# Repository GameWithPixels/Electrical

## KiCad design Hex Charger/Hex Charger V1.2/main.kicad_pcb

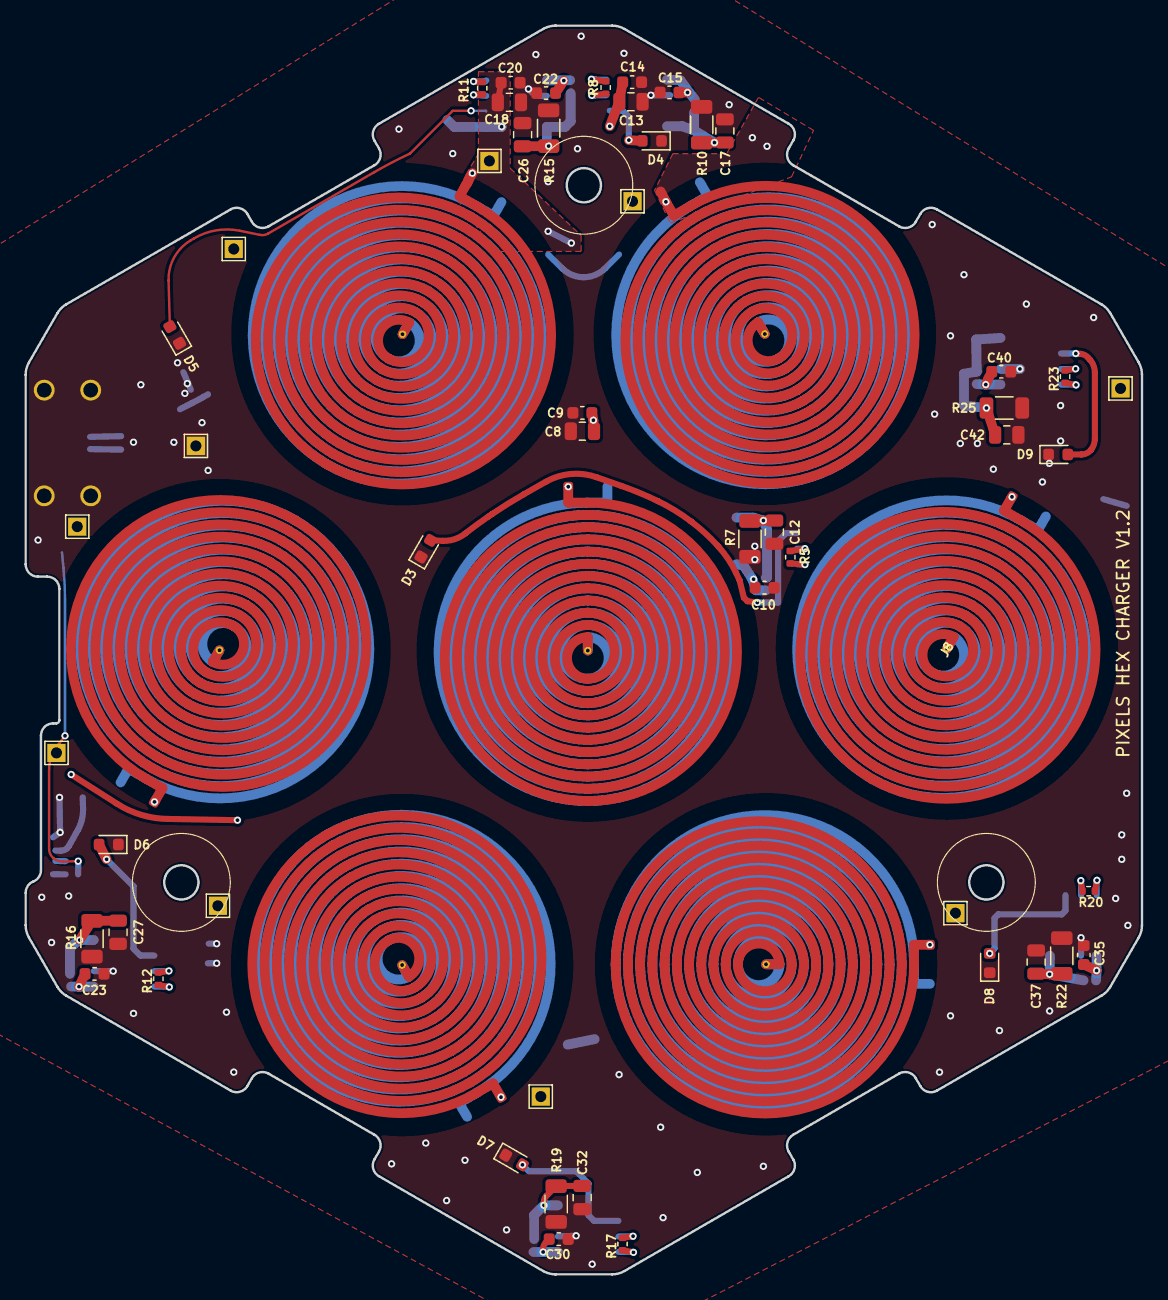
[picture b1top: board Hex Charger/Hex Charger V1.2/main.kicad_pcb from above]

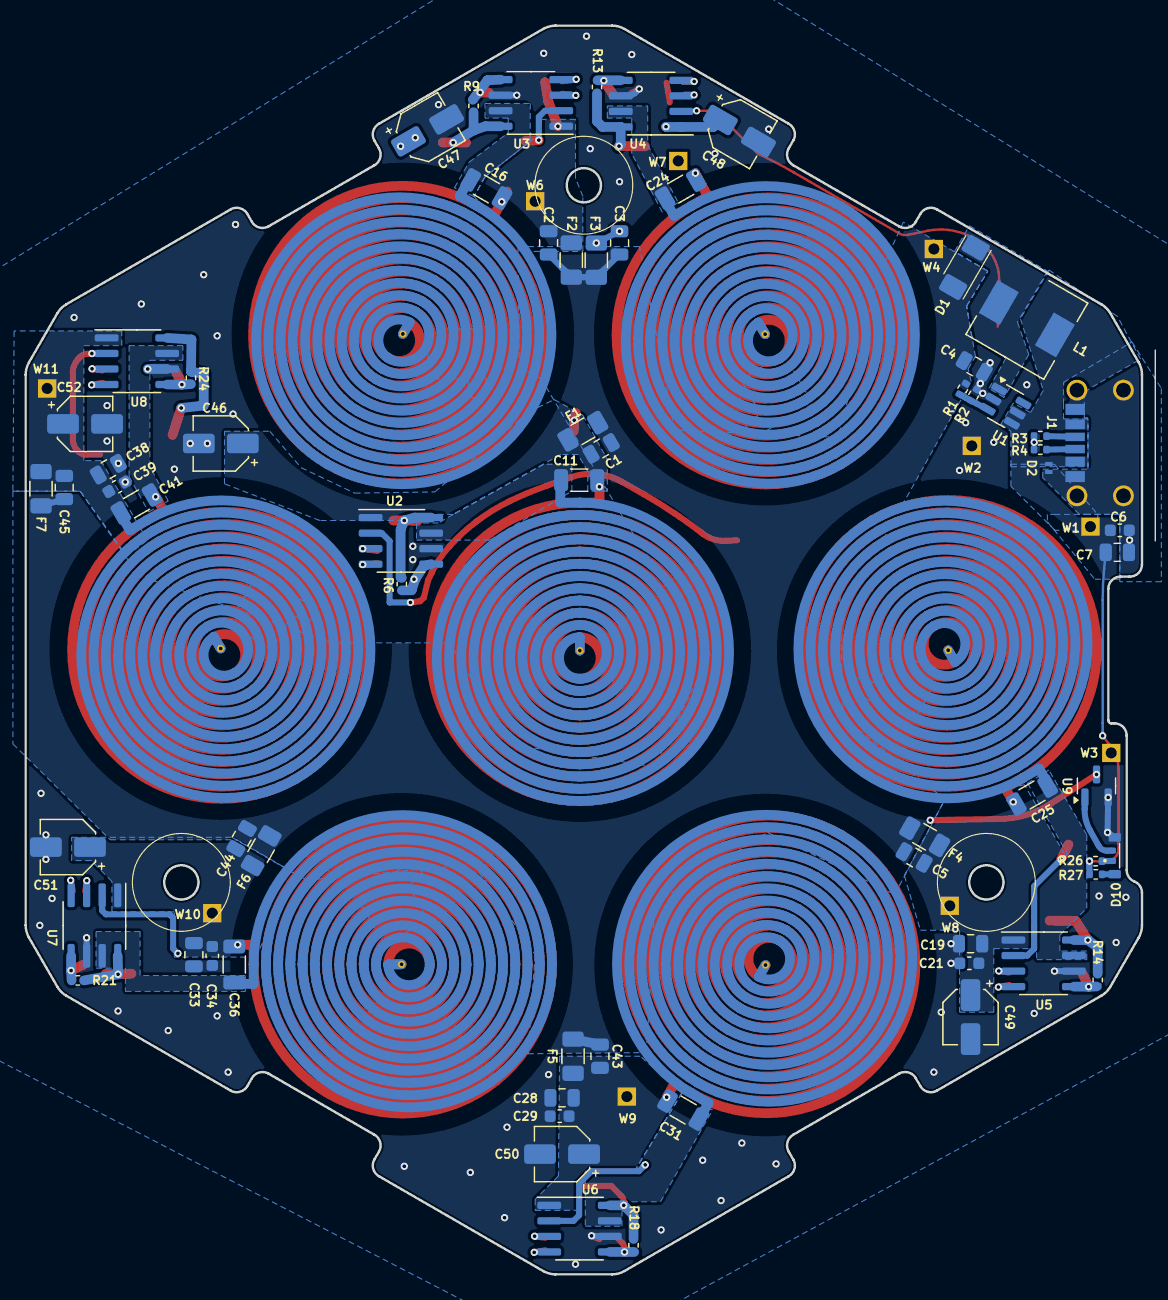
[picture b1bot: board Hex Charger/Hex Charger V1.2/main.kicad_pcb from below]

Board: 2 copper layers, 91.3 x 102.1 mm, 124 parts (72 on the bottom side), 59 nets.

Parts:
C1, C2, C3, C5, C12, C17, C26, C27, C32, C37, C42, C43, C44, C45: 10uF 50V 10% X5R; C_0805_2012Metric
C4, C7, C8, C13, C18, C19, C28, C33, C38: 22uF 25V 20% X5R; C_0805_2012Metric
C6, C9, C10, C14, C15, C20, C21, C22, C23, C29, C30, C34, C35, C39, C40: 0.1uF 16V 10% X7R; C_0603_1608Metric
C11, C16, C24, C25, C31, C36, C41: 33nF 50V COG; C_1206_3216Metric
C46, C47, C48, C49, C50, C51, C52: 100uF 10V 20%; CP_Elec_4x5.4
D1: D; SMAF
D2: D_TVS; DFN
D3, D4, D5, D6, D7, D8, D9: LED; LED_0603_1608Metric
D10: LED_Dual_KKAA; XL-3210SURUGC
F1, F2, F3, F4, F5, F6, F7: 250mA 150mR; Fuse_1206_3216Metric
J1: USB_C_Receptacle_USB2.0; USB-C-SMD_10P-P1.00-L6.8-W8.9
J2, J3, J4, J5, J6, J7, J8: Conn_01x02_Socket; PCB Coil 25_11_0.8_0.2
L1: 10uH 500mA; L_Wuerth_HCM-7050
R1: 470k; R_0402_1005Metric
R2: 52.3k; R_0402_1005Metric
R3, R4: 5.1k 1%; R_0402_1005Metric
R5, R8, R11, R12, R17, R20, R23: 120K 1%; R_0402_1005Metric
R6, R9, R13, R14, R18, R21, R24: 1k 1%; R_0402_1005Metric
R7, R10, R15, R16, R19, R22, R25: 0.91R; R_1206_3216Metric
R26, R27: 200R 5%; R_0402_1005Metric
U1: MT3608B; SOT-23-6
U2, U3, U4, U5, U6, U7, U8: XKT520; SOIC-8_3.9x4.9mm_P1.27mm
U9: SSP61CN4802MR; SOT-23
W1: VBUS; TestPoint_1.5x1.5_Drill0.9mm
W2: GND; TestPoint_1.5x1.5_Drill0.9mm
W3: 5V; TestPoint_1.5x1.5_Drill0.9mm
W4: VCC; TestPoint_1.5x1.5_Drill0.9mm
W6, W7, W8, W9, W10, W11: +6V; TestPoint_1.5x1.5_Drill0.9mm

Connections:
+5V: C6.1, C7.1, D2.1 (A1), J1.A9 (VBUS), J1.B9 (VBUS), L1.1, R26.2, R27.2, U1.4 (EN), U1.5 (IN), W1.1, W3.1
/Charger1/+6V: C1.1, C8.1, C9.1, C11.2, C46.1, F1.2, J2.2, U2.1 (VDD)
/Charger1/VCC: C1.2, C2.2, C3.2, C4.1, C5.2, C43.2, C44.2, C45.2, D1.1 (K), F1.1, F2.1, F3.1, F4.1, F5.1, F6.1, F7.1, R1.1, U9.3 (VIN), W4.1
/Charger2/+6V: C2.1, C13.1, C14.1, C16.2, C47.1, F2.2, J3.2, U3.1 (VDD), W6.1
/Charger3/+6V: C3.1, C18.1, C20.1, C24.2, C48.1, F3.2, J4.2, U4.1 (VDD), W7.1
/Charger4/+6V: C5.1, C19.1, C21.1, C25.2, C49.1, F4.2, J5.2, U5.1 (VDD), W8.1
/Charger5/+6V: C28.1, C29.1, C31.2, C43.1, C50.1, F5.2, J6.2, U6.1 (VDD), W9.1
/Charger6/+6V: C33.1, C34.1, C36.2, C44.1, C51.1, F6.2, J7.2, U7.1 (VDD), W10.1
/Charger7/+6V: C38.1, C39.1, C41.2, C45.1, C52.1, F7.2, J8.2, U8.1 (VDD), W11.1
/SW: D1.2 (A), L1.2, U1.1 (SW)
GND: C4.2, C6.2, C7.2, C8.2, C9.2, C10.1, C12.2, C13.2, C14.2, C15.1, C17.2, C18.2, C19.2, C20.2, C21.2, C22.1, C23.1, C26.2, C27.2, C28.2, C29.2, C30.1, C32.2, C33.2, C34.2, C35.1, C37.2, C38.2, C39.2, C40.1, C42.2, C46.2, C47.2, C48.2, C49.2, C50.2, C51.2, C52.2, D2.2 (A2), D3.1 (K), D4.1 (K), D5.1 (K), D6.1 (K), D7.1 (K), D8.1 (K), D9.1 (K), D10.4 (K2), J1.A12 (GND), J1.B12 (GND), J1.S1 (SHIELD), R2.2, R3.1, R4.1, R7.1, R10.1, R15.1, R16.1, R19.1, R22.1, R25.1, U1.2 (GND), U2.6 (VSS), U3.6 (VSS), U4.6 (VSS), U5.6 (VSS), U6.6 (VSS), U7.6 (VSS), U8.6 (VSS), U9.2 (GND), W2.1
unnamed: D3.2 (A), U2.2 (LED)
unnamed: D4.2 (A), U3.2 (LED)
unnamed: D5.2 (A), U4.2 (LED)
unnamed: D6.2 (A), U5.2 (LED)
unnamed: D7.2 (A), U6.2 (LED)
unnamed: D8.2 (A), U7.2 (LED)
unnamed: D9.2 (A), U8.2 (LED)
unnamed: D10.1 (A1), R26.1
unnamed: D10.3 (A2), R27.1
unnamed: D10.2 (K1), U9.1 (VOUT)
unnamed: J1.A5 (CC1), R4.2
unnamed: J1.B5 (CC2), R3.2
unnamed: C11.1, J2.1, U2.7 (OUT)
unnamed: C16.1, J3.1, U3.7 (OUT)
unnamed: C24.1, J4.1, U4.7 (OUT)
unnamed: C25.1, J5.1, U5.7 (OUT)
unnamed: C31.1, J6.1, U6.7 (OUT)
unnamed: C36.1, J7.1, U7.7 (OUT)
unnamed: C41.1, J8.1, U8.7 (OUT)
unnamed: R5.1, U2.4 (R)
unnamed: R5.2, U2.3 (R)
unnamed: R8.1, U3.4 (R)
unnamed: R8.2, U3.3 (R)
unnamed: R11.1, U4.4 (R)
unnamed: R11.2, U4.3 (R)
unnamed: R12.1, U5.4 (R)
unnamed: R12.2, U5.3 (R)
unnamed: R17.1, U6.4 (R)
unnamed: R17.2, U6.3 (R)
unnamed: R20.1, U7.4 (R)
unnamed: R20.2, U7.3 (R)
unnamed: R23.1, U8.4 (R)
unnamed: R23.2, U8.3 (R)
unnamed: R1.2, R2.1, U1.3 (FB)
unnamed: C10.2, R6.1, U2.5 (FB)
unnamed: C12.1, R6.2, R7.2, U2.8 (PVSS)
unnamed: C15.2, R9.1, U3.5 (FB)
unnamed: C17.1, R9.2, R10.2, U3.8 (PVSS)
unnamed: C22.2, R13.1, U4.5 (FB)
unnamed: C26.1, R13.2, R15.2, U4.8 (PVSS)
unnamed: C23.2, R14.1, U5.5 (FB)
unnamed: C27.1, R14.2, R16.2, U5.8 (PVSS)
unnamed: C30.2, R18.1, U6.5 (FB)
unnamed: C32.1, R18.2, R19.2, U6.8 (PVSS)
unnamed: C35.2, R21.1, U7.5 (FB)
unnamed: C37.1, R21.2, R22.2, U7.8 (PVSS)
unnamed: C40.2, R24.1, U8.5 (FB)
unnamed: C42.1, R24.2, R25.2, U8.8 (PVSS)

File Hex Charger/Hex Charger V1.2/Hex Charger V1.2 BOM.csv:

"Reference","Value","Datasheet","Footprint","Qty","DNP","Manufacturer","Part Number","LCSC Part #"
"C1,C2,C3,C5,C12,C17,C26,C27,C32,C37,C42,C43,C44,C45","10uF 50V 10% X5R","~","Capacitor_SMD:C_0805_2012Metric","14","","Murata","GRM21BR61H106KE43L","C440198"
"C4,C7,C8,C13,C18,C19,C28,C33,C38","22uF 25V 20% X5R","~","Capacitor_SMD:C_0805_2012Metric","9","","Murata","GRM21BR61E226ME44L","C86816"
"C6,C9,C10,C14,C15,C20,C21,C22,C23,C29,C30,C34,C35,C39,C40","0.1uF 16V 10% X7R","~","Capacitor_SMD:C_0603_1608Metric","15","","Samsung Electro-Mechanics","CL10B104KO8NNNC","C66501"
"C11,C16,C24,C25,C31,C36,C41","33nF 50V COG","~","Capacitor_SMD:C_1206_3216Metric","7","","Murata","GRM3195C1H333JA01D","C97930"
"C46,C47,C48,C49,C50,C51,C52","100uF 10V 20%","~","Capacitor_SMD:CP_Elec_4x5.4","7","","ROQANG","CK1A470M-CRC54","C3001223"
"D1","D","~","Pixels-dice:SMAF","1","","GOODWORK","SS54F","C908671"
"D2","D_TVS","~","Pixels-dice:DFN","1","","Murata","LXES1UTAA1-157","C5210979"
"D3,D4,D5,D6,D7,D8,D9","LED","~","LED_SMD:LED_0603_1608Metric","7","","Lite-On","LTST-C191KRKT","C125099"
"D10","LED_Dual_KKAA","~","Pixels-dice:XL-3210SURUGC","1","","XINGLIGHT","XL-3210SURUGC","C965883"
"F1,F2,F3,F4,F5,F6,F7","250mA 150mR","~","Fuse:Fuse_1206_3216Metric","7","","BHFUSE","BSMD1206-025-33V","C2977524"
"J1","USB_C_Receptacle_USB2.0","https://www.usb.org/sites/default/files/documents/usb_type-c.zip","Pixels-dice:USB-C-SMD_10P-P1.00-L6.8-W8.9","1","","Korean Hroparts Elec","TYPE-C-31-M-17","C283540"
"J2,J3,J4,J5,J6,J7,J8","Conn_01x02_Socket","~","Pixels-dice:PCB Coil 25_11_0.8_0.2","7","DNP","","",""
"L1","10uH 500mA","~","Inductor_SMD:L_Wuerth_HCM-7050","1","","Ruishen","RS0650-100MS","C32712977"
"R1","470k","~","Resistor_SMD:R_0402_1005Metric","1","","UNI-ROYAL(Uniroyal Elec)","0402WGF4703TCE","C25790"
"R2","52.3k","~","Resistor_SMD:R_0402_1005Metric","1","","UNI-ROYAL(Uniroyal Elec)","0402WGF5232TCE","C26982"
"R3,R4","5.1k 1%","~","Resistor_SMD:R_0402_1005Metric","2","","UNI-ROYAL(Uniroyal Elec)","0402WGF5101TCE","C25905"
"R5,R8,R11,R12,R17,R20,R23","120K 1%","~","Resistor_SMD:R_0402_1005Metric","7","","UNI-ROYAL(Uniroyal Elec)","0402WGF1203TCE","C25750"
"R6,R9,R13,R14,R18,R21,R24","1k 1%","~","Resistor_SMD:R_0402_1005Metric","7","","UNI-ROYAL(Uniroyal Elec)","0402WGF1001TCE","C11702"
"R7,R10,R15,R16,R19,R22,R25","0.91R","~","Resistor_SMD:R_1206_3216Metric","7","","YAGEO","RL1206FR-7W0R91L","C136987"
"R26,R27","200R 5%","~","Resistor_SMD:R_0402_1005Metric","2","","UNI-ROYAL(Uniroyal Elec)","0402WGF2000TCE","C25087"
"U1","MT3608B","https://www.olimex.com/Products/Breadboarding/BB-PWR-3608/re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","Package_TO_SOT_SMD:SOT-23-6","1","","XI'AN Aerosemi Tech","MT3608B","C19189893"
"U2,U3,U4,U5,U6,U7,U8","XKT520","","Pixels-dice:SOIC-8_3.9x4.9mm_P1.27mm","7","","XKT","520",""
"U9","SSP61CN4802MR","","Package_TO_SOT_SMD:SOT-23","1","","UMW(Youtai Semiconductor Co., Ltd.)","HT7050S","C2842953"
"W1","VBUS","","Pixels-dice:TestPoint_1.5x1.5_Drill0.9mm","1","","","",""
"W2","GND","","Pixels-dice:TestPoint_1.5x1.5_Drill0.9mm","1","","","",""
"W3","5V","","Pixels-dice:TestPoint_1.5x1.5_Drill0.9mm","1","","","",""
"W4","VCC","","Pixels-dice:TestPoint_1.5x1.5_Drill0.9mm","1","","","",""
"W5,W6,W7,W8,W9,W10,W11","+6V","","Pixels-dice:TestPoint_1.5x1.5_Drill0.9mm","7","","","",""

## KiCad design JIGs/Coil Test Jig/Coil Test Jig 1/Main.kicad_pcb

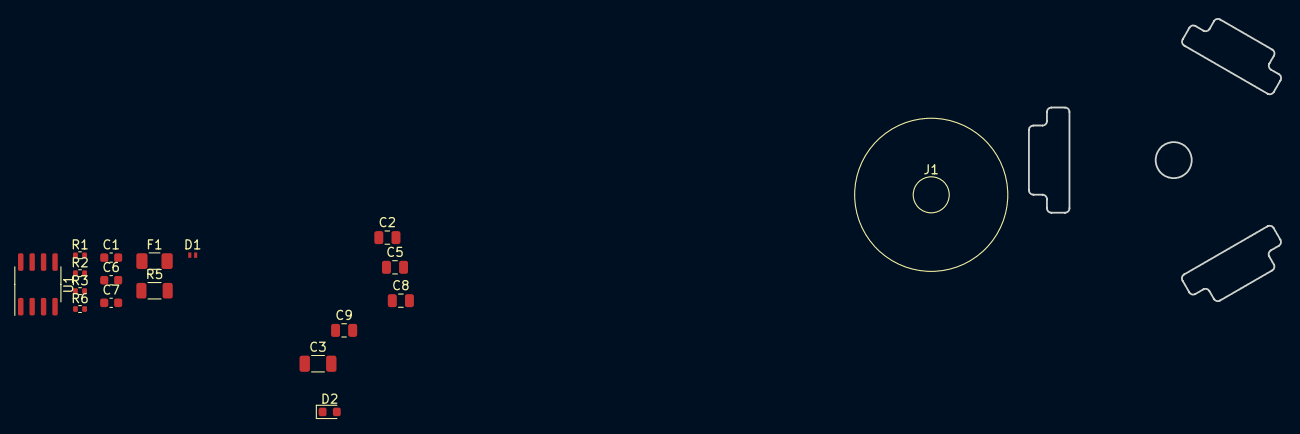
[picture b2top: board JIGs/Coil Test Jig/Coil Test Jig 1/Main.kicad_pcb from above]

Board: 4 copper layers, 18 parts (0 on the bottom side), 9 nets, no tracks yet.

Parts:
C1, C6, C7: 0.1uF 16V 10% X7R; C_0603_1608Metric
C2, C5: 22uF 25V 20% X5R; C_0805_2012Metric
C3: 33nF 50V COG; C_1206_3216Metric
C8, C9: 10uF 50V 10% X5R; C_0805_2012Metric
D1: D_TVS; DFN
D2: LED; LED_0603_1608Metric
F1: 250mA 150mR; Fuse_1206_3216Metric
J1: TX_Coil; TX Coil
R1, R2: 5.1k 1%; R_0402_1005Metric
R3: 120K 1%; R_0402_1005Metric
R5: 0.91R; R_1206_3216Metric
R6: 1k 1%; R_0402_1005Metric
U1: XKT520; SOIC-8_3.9x4.9mm_P1.27mm

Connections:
+5V: C1.1, C2.1, C3.2, C5.1, C7.1, C8.1, F1.2, U1.1 (VDD)
GND: C1.2, C2.2, C5.2, C6.1, C7.2, C9.2, D1.2 (A2), D2.1 (K), R1.1, R2.1, R5.1, U1.6 (VSS)
GNDPWR: C9.1, R5.2, R6.2, U1.8 (PVSS)
unnamed: D2.2 (A), U1.2 (LED)
unnamed: C3.1, U1.7 (OUT)
unnamed: R3.1, U1.4 (R)
unnamed: R3.2, U1.3 (R)
unnamed: C6.2, R6.1, U1.5 (FB)
VBUS: C8.2, D1.1 (A1), F1.1

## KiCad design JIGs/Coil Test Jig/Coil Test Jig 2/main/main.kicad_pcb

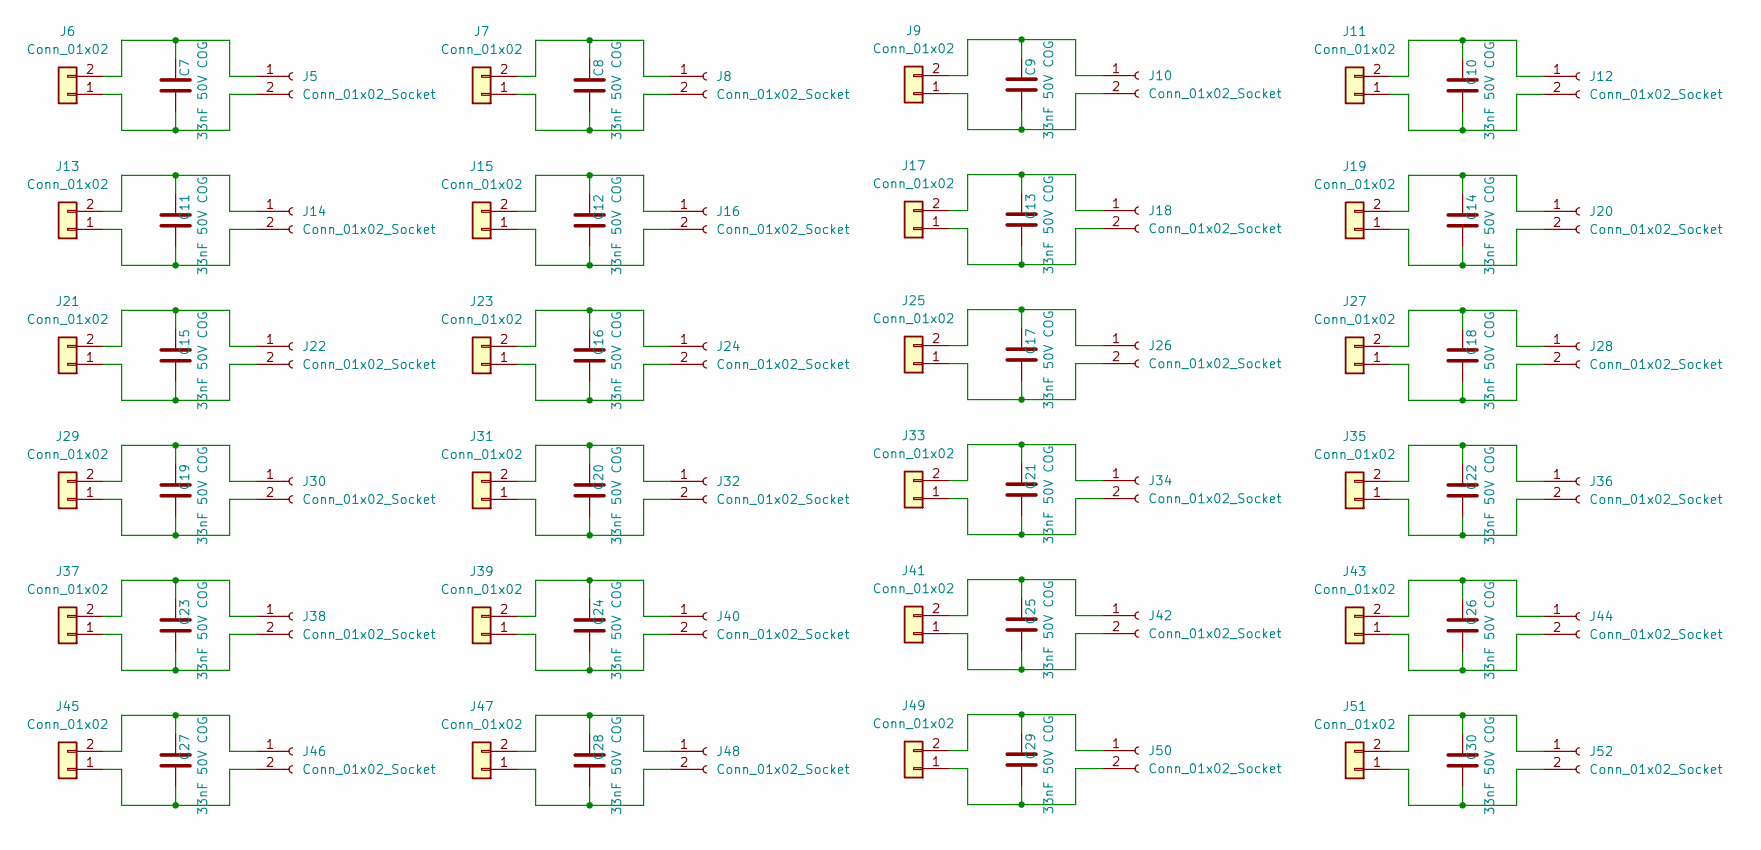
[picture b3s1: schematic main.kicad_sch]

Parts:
C7, C8, C9, C10, C11, C12, C13, C14, C15, C16, C17, C18, C19, C20, C21, C22, C23, C24, C25, C26, C27, C28, C29, C30: 33nF 50V COG; C_1206_3216Metric; Part Number GRM3195C1H333JA01J
J5, J8, J10, J12, J14, J16, J18, J20, J22, J24, J26, J28, J30, J32, J34, J36, J38, J40, J42, J44, J46, J48, J50, J52: Conn_01x02_Socket; PinHeader_2x01_P1.00mm_Vertical
J6, J7, J9, J11, J13, J15, J17, J19, J21, J23, J25, J27, J29, J31, J33, J35, J37, J39, J41, J43, J45, J47, J49, J51: Conn_01x02; Coil_Pins

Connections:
unnamed: C7.2, J5.1, J6.2
unnamed: C7.1, J5.2, J6.1
unnamed: C8.1, J7.1, J8.2
unnamed: C8.2, J7.2, J8.1
unnamed: C9.2, J9.2, J10.1
unnamed: C9.1, J9.1, J10.2
unnamed: C10.1, J11.1, J12.2
unnamed: C10.2, J11.2, J12.1
unnamed: C11.1, J13.1, J14.2
unnamed: C11.2, J13.2, J14.1
unnamed: C12.1, J15.1, J16.2
unnamed: C12.2, J15.2, J16.1
unnamed: C13.1, J17.1, J18.2
unnamed: C13.2, J17.2, J18.1
unnamed: C14.1, J19.1, J20.2
unnamed: C14.2, J19.2, J20.1
unnamed: C15.1, J21.1, J22.2
unnamed: C15.2, J21.2, J22.1
unnamed: C16.1, J23.1, J24.2
unnamed: C16.2, J23.2, J24.1
unnamed: C17.1, J25.1, J26.2
unnamed: C17.2, J25.2, J26.1
unnamed: C18.1, J27.1, J28.2
unnamed: C18.2, J27.2, J28.1
unnamed: C19.1, J29.1, J30.2
unnamed: C19.2, J29.2, J30.1
unnamed: C20.1, J31.1, J32.2
unnamed: C20.2, J31.2, J32.1
unnamed: C21.1, J33.1, J34.2
unnamed: C21.2, J33.2, J34.1
unnamed: C22.1, J35.1, J36.2
unnamed: C22.2, J35.2, J36.1
unnamed: C23.1, J37.1, J38.2
unnamed: C23.2, J37.2, J38.1
unnamed: C24.1, J39.1, J40.2
unnamed: C24.2, J39.2, J40.1
unnamed: C25.1, J41.1, J42.2
unnamed: C25.2, J41.2, J42.1
unnamed: C26.1, J43.1, J44.2
unnamed: C26.2, J43.2, J44.1
unnamed: C27.1, J45.1, J46.2
unnamed: C27.2, J45.2, J46.1
unnamed: C28.1, J47.1, J48.2
unnamed: C28.2, J47.2, J48.1
unnamed: C29.1, J49.1, J50.2
unnamed: C29.2, J49.2, J50.1
unnamed: C30.1, J51.1, J52.2
unnamed: C30.2, J51.2, J52.1

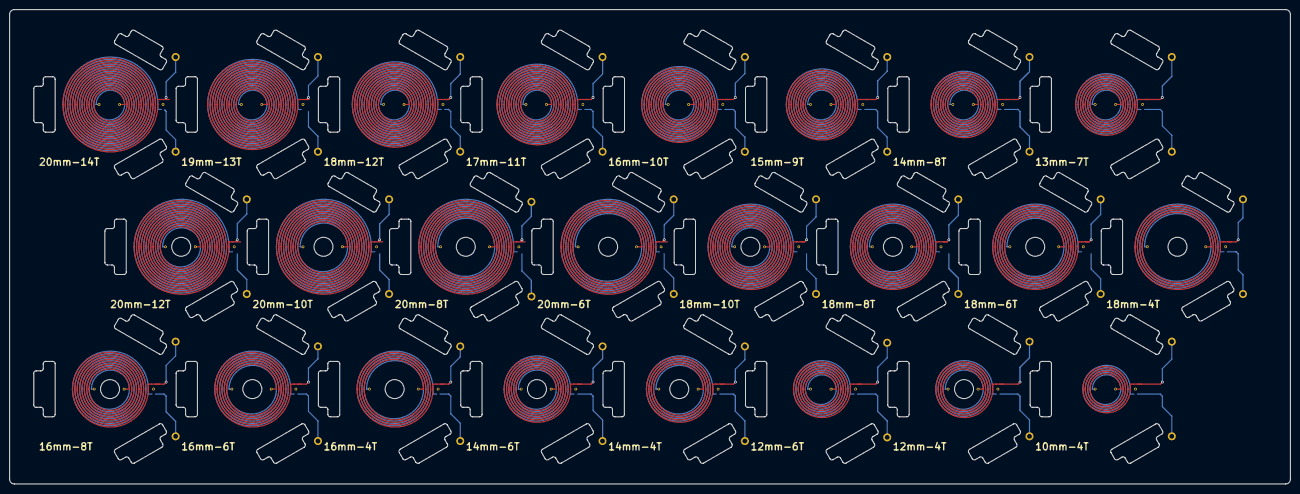
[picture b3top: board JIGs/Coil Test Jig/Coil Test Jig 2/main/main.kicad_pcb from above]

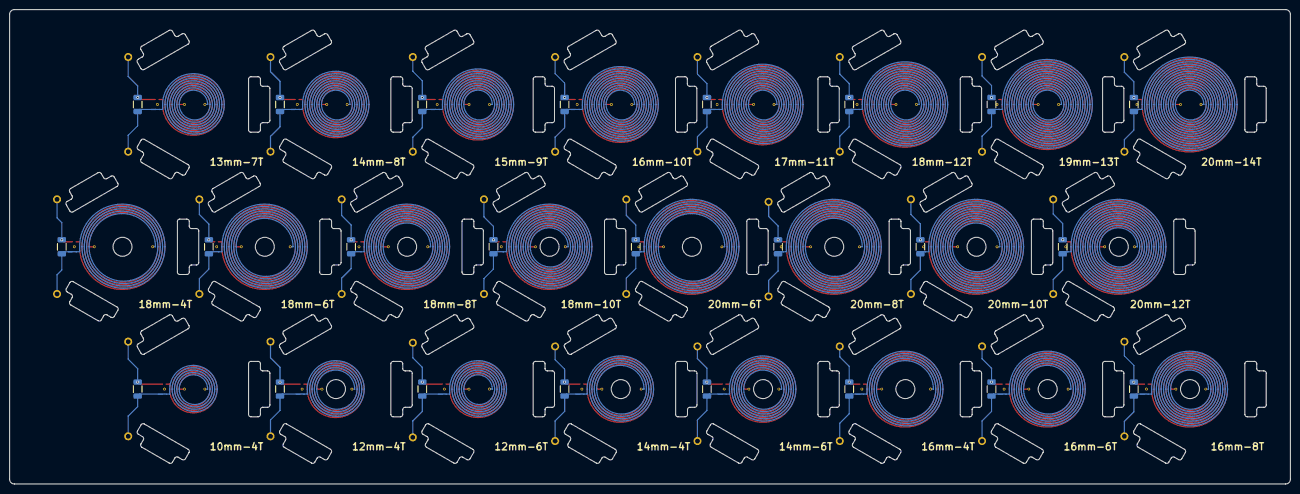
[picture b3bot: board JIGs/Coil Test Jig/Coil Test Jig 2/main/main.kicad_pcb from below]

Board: 4 copper layers, 270.0 x 100.0 mm, 72 parts (45 on the bottom side), 48 nets.

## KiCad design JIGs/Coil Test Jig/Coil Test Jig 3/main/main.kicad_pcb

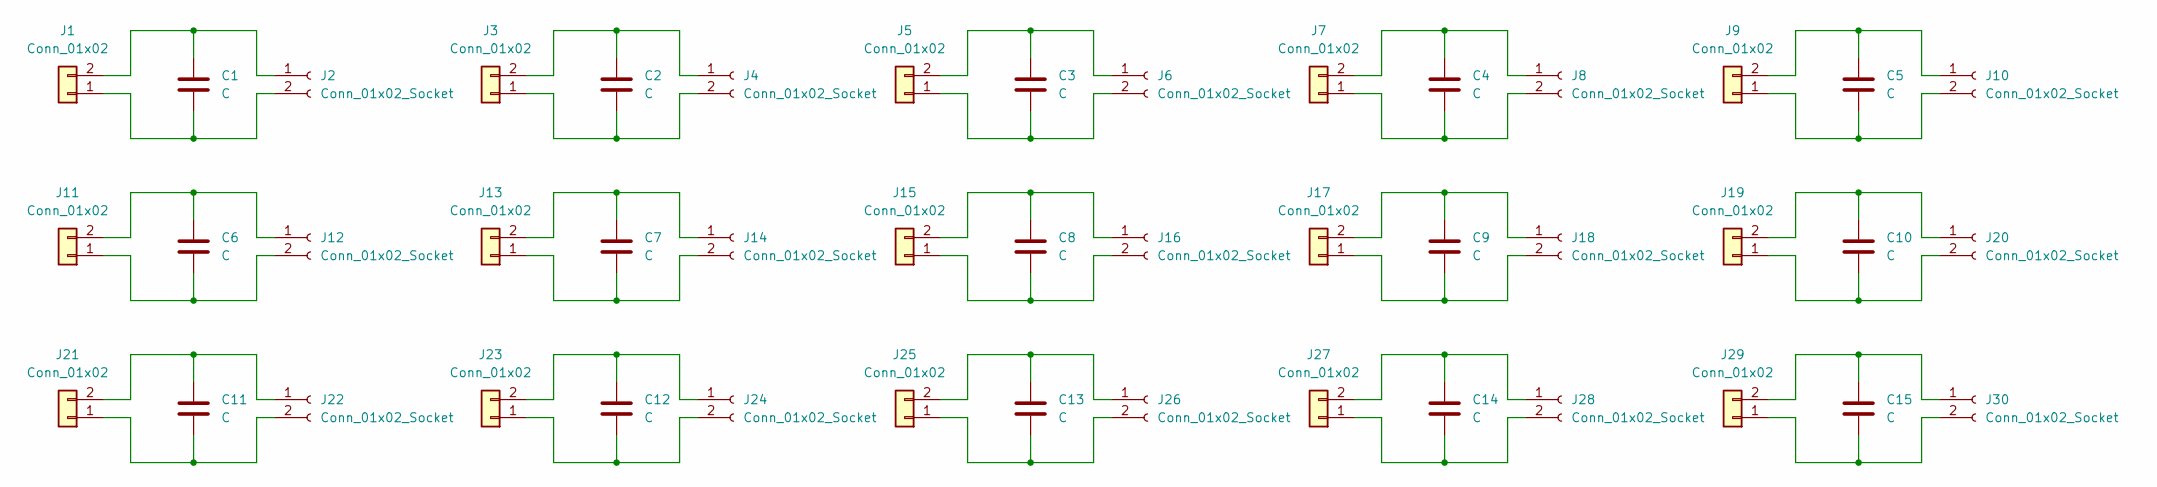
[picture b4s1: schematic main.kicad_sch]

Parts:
C1, C2, C3, C4, C5, C6, C7, C8, C9, C10, C11, C12, C13, C14, C15: C; C_1206_3216Metric
J1, J3, J5, J7, J9, J11, J13, J15, J17, J19, J21, J23, J25, J27, J29: Conn_01x02; PinHeader_2x01_P1.00mm_Vertical
J2, J4, J6, J8, J10, J12, J14, J16, J18, J20, J22, J24, J26, J28, J30: Conn_01x02_Socket; Coil_Con

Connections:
unnamed: C1.2, J1.1, J2.2
unnamed: C1.1, J1.2, J2.1
unnamed: C2.2, J3.1, J4.2
unnamed: C2.1, J3.2, J4.1
unnamed: C3.2, J5.1, J6.2
unnamed: C3.1, J5.2, J6.1
unnamed: C4.2, J7.1, J8.2
unnamed: C4.1, J7.2, J8.1
unnamed: C5.1, J9.2, J10.1
unnamed: C5.2, J9.1, J10.2
unnamed: C6.2, J11.1, J12.2
unnamed: C6.1, J11.2, J12.1
unnamed: C7.2, J13.1, J14.2
unnamed: C7.1, J13.2, J14.1
unnamed: C8.2, J15.1, J16.2
unnamed: C8.1, J15.2, J16.1
unnamed: C9.2, J17.1, J18.2
unnamed: C9.1, J17.2, J18.1
unnamed: C10.2, J19.1, J20.2
unnamed: C10.1, J19.2, J20.1
unnamed: C11.2, J21.1, J22.2
unnamed: C11.1, J21.2, J22.1
unnamed: C12.2, J23.1, J24.2
unnamed: C12.1, J23.2, J24.1
unnamed: C13.2, J25.1, J26.2
unnamed: C13.1, J25.2, J26.1
unnamed: C14.2, J27.1, J28.2
unnamed: C14.1, J27.2, J28.1
unnamed: C15.2, J29.1, J30.2
unnamed: C15.1, J29.2, J30.1

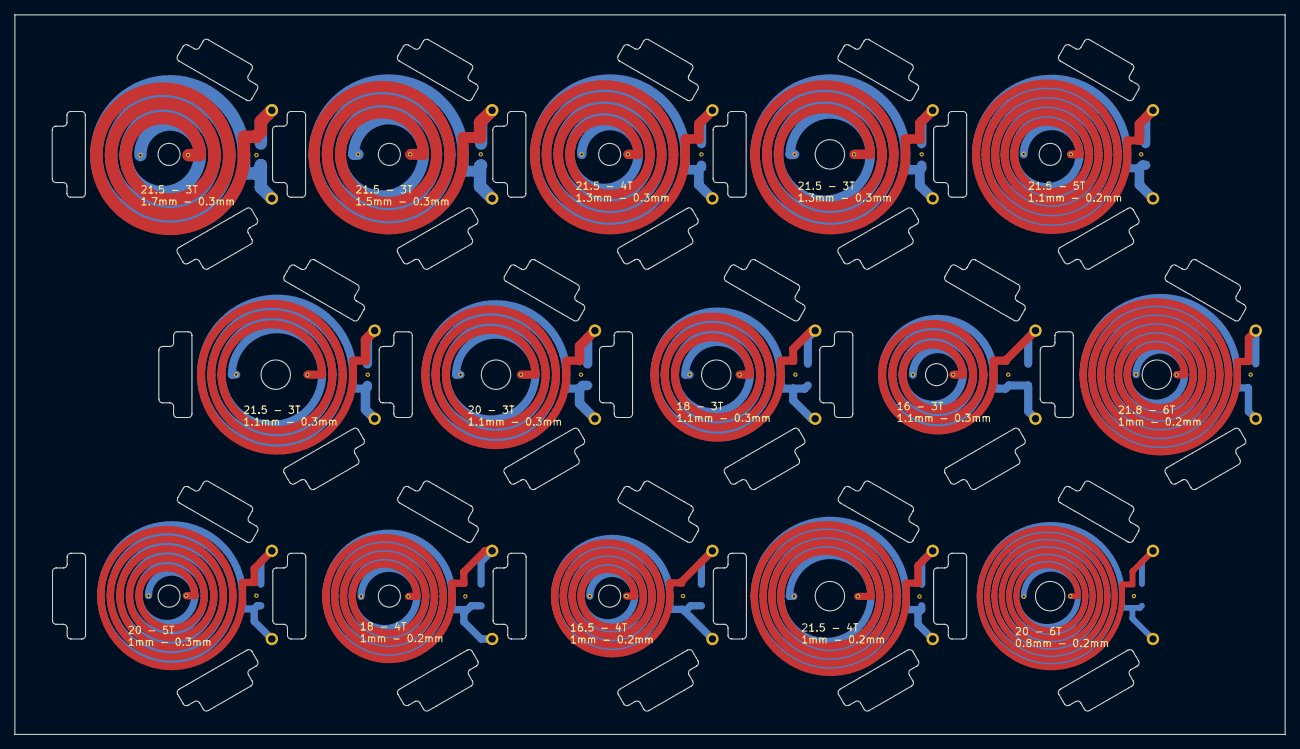
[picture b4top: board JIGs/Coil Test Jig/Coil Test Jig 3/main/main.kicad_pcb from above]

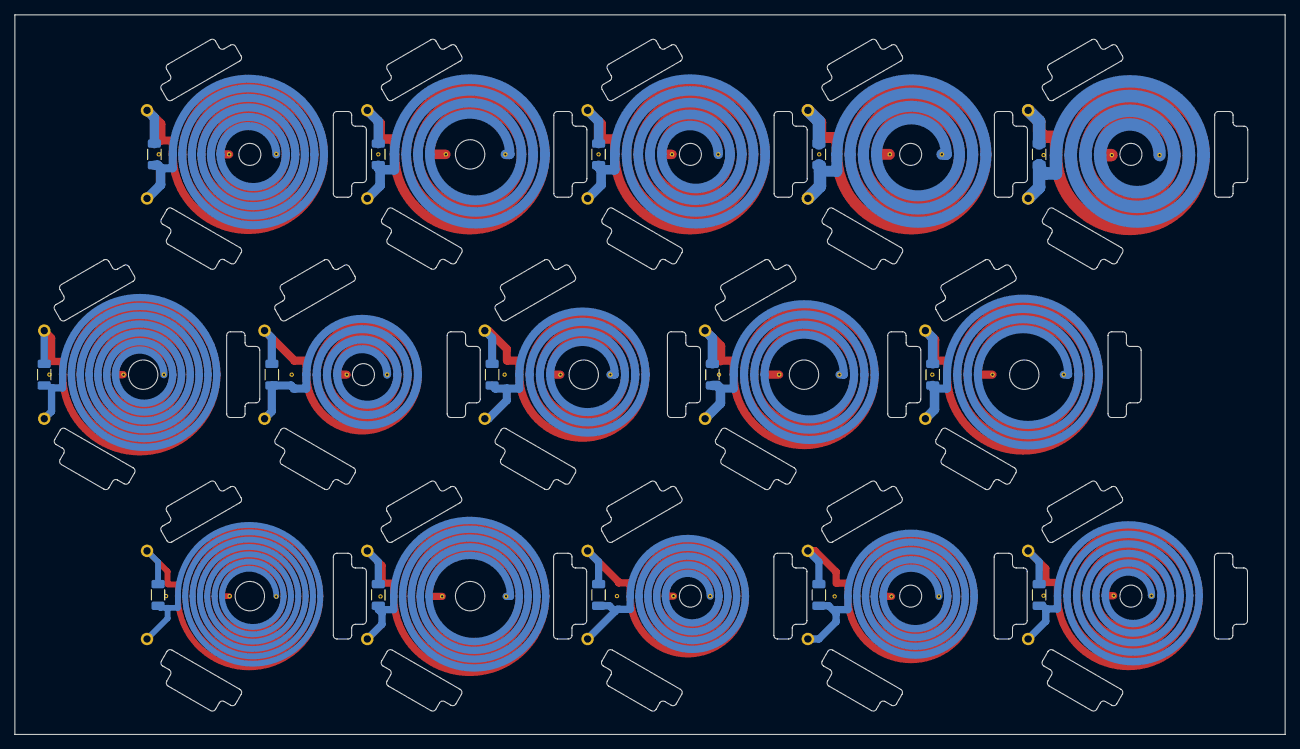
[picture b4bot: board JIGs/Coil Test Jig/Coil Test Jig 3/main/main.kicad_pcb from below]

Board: 4 copper layers, 173.0 x 98.0 mm, 45 parts (15 on the bottom side), 30 nets.

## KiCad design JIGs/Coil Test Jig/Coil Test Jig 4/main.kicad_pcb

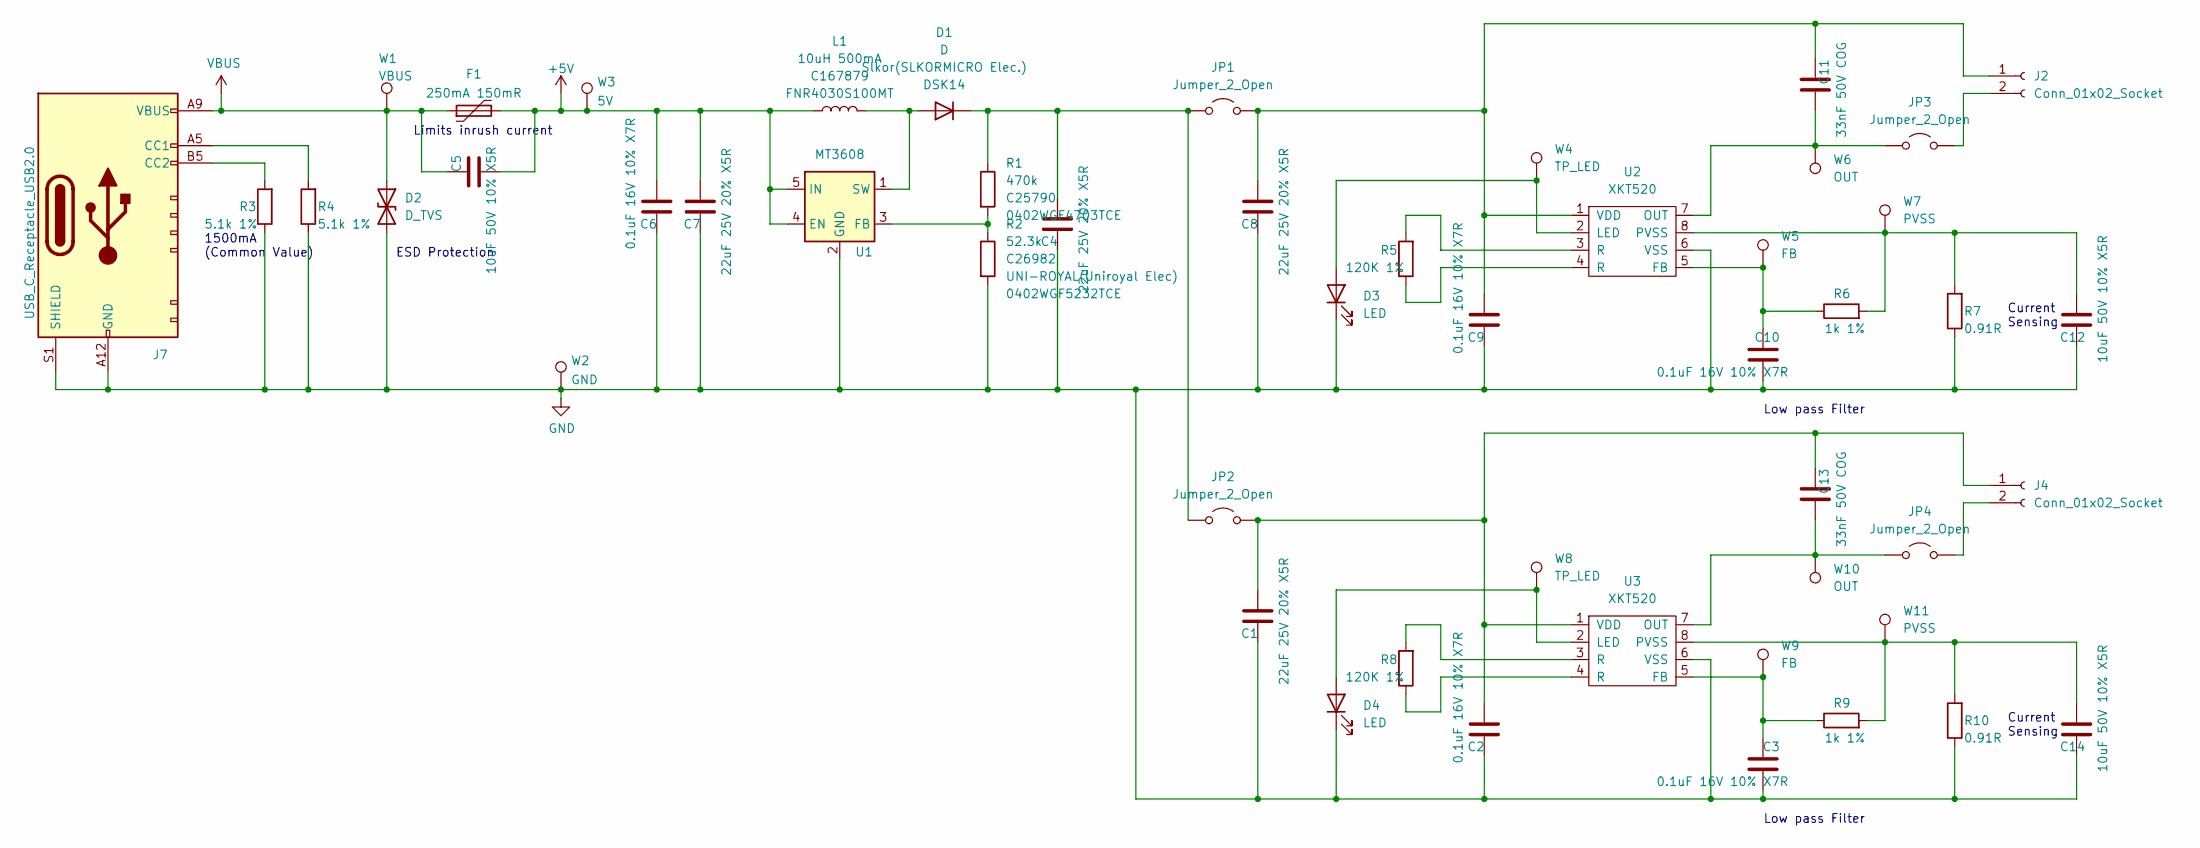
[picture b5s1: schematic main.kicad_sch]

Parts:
C1, C4, C7, C8: 22uF 25V 20% X5R; C_0805_2012Metric; Part Number GRM21BR61E226ME44L; LCSC Part Number C86816
C2, C3, C6, C9, C10: 0.1uF 16V 10% X7R; C_0603_1608Metric; Part Number CL10B104KO8NNNC; LCSC Part Number C66501
C5, C12, C14: 10uF 50V 10% X5R; C_0805_2012Metric; Part Number GRM21BR61H106KE43L; LCSC Part Number C440198
C11, C13: 33nF 50V COG; C_1206_3216Metric; Part Number GRM3195C1H333JA01D; LCSC Part Number C97930
D1: D; Nexperia_CFP3_SOD-123W; Part Number DSK14; LCSC Part Number C2760892
D2: D_TVS; DFN; Part Number LXES1UTAA1-157; LCSC Part Number C5210979
D3, D4: LED; LED_0603_1608Metric; Part Number LTST-C191KRKT; LCSC Part Number C125099
F1: 250mA 150mR; Fuse_1206_3216Metric; Part Number BSMD1206-025-33V; LCSC Part Number C2977524
J2, J4: Conn_01x02_Socket; Coil_Con
J7: USB_C_Receptacle_USB2.0; USB-C-SMD_10P-P1.00-L6.8-W8.9; Part Number TYPE-C-31-M-17; LCSC Part Number C283540
JP1, JP2, JP3, JP4: Jumper_2_Open; PinHeader_1x02_P2.54mm_Vertical
L1: 10uH 500mA; L_Taiyo-Yuden_MD-4040; Part Number FNR4030S100MT; LCSC Part Number C167879
R1: 470k; R_0402_1005Metric; Part Number 0402WGF4703TCE; LCSC Part Number C25790
R2: 52.3k; R_0402_1005Metric; Part Number 0402WGF5232TCE; LCSC Part Number C26982
R3, R4: 5.1k 1%; R_0402_1005Metric; Part Number 0402WGF5101TCE; LCSC Part Number C25905
R5, R8: 120K 1%; R_0402_1005Metric; Part Number 0402WGF1203TCE; LCSC Part Number C25750
R6, R9: 1k 1%; R_0402_1005Metric; Part Number 0402WGF1001TCE; LCSC Part Number C11702
R7, R10: 0.91R; R_1206_3216Metric; Part Number RL1206FR-7W0R91L; LCSC Part Number C136987
U1: MT3608; SOT-23-6; Part Number MT3608; LCSC Part Number C84817
U2, U3: XKT520; SOIC-8_3.9x4.9mm_P1.27mm
W1: VBUS; TestPoint_1.5x1.5_Drill0.9mm
W2: GND; TestPoint_1.5x1.5_Drill0.9mm
W3: 5V; TestPoint_1.5x1.5_Drill0.9mm
W4, W8: TP_LED; TestPoint_1.5x1.5_Drill0.9mm
W5, W9: FB; TestPoint_1.5x1.5_Drill0.9mm
W6, W10: OUT; TestPoint_1.5x1.5_Drill0.9mm
W7, W11: PVSS; TestPoint_1.5x1.5_Drill0.9mm

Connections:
+5V: C5.1, C6.1, C7.1, F1.2, L1.1, U1.4 (EN), U1.5 (IN), W3.1
GND: C1.2, C2.2, C3.1, C4.2, C6.2, C7.2, C8.2, C9.2, C10.1, C12.2, C14.2, D2.2 (A2), D3.1 (K), D4.1 (K), J7.A12 (GND), J7.B12 (GND), J7.S1 (SHIELD), R2.2, R3.1, R4.1, R7.1, R10.1, U1.2 (GND), U2.6 (VSS), U3.6 (VSS), W2.1
unnamed: D1.2 (A), L1.2, U1.1 (SW)
unnamed: C4.1, D1.1 (K), JP1.1 (A), JP2.1 (A), R1.1
unnamed: D3.2 (A), U2.2 (LED), W4.1
unnamed: D4.2 (A), U3.2 (LED), W8.1
unnamed: C8.1, C9.1, C11.2, J2.1, JP1.2 (B), U2.1 (VDD)
unnamed: J2.2, JP3.2 (B)
unnamed: C1.1, C2.1, C13.2, J4.1, JP2.2 (B), U3.1 (VDD)
unnamed: J4.2, JP4.2 (B)
unnamed: J7.A5 (CC1), R4.2
unnamed: J7.B5 (CC2), R3.2
unnamed: C11.1, JP3.1 (A), U2.7 (OUT), W6.1
unnamed: C13.1, JP4.1 (A), U3.7 (OUT), W10.1
unnamed: R5.1, U2.4 (R)
unnamed: R5.2, U2.3 (R)
unnamed: R8.1, U3.4 (R)
unnamed: R8.2, U3.3 (R)
unnamed: R1.2, R2.1, U1.3 (FB)
unnamed: C10.2, R6.1, U2.5 (FB), W5.1
unnamed: C12.1, R6.2, R7.2, U2.8 (PVSS), W7.1
unnamed: C3.2, R9.1, U3.5 (FB), W9.1
unnamed: C14.1, R9.2, R10.2, U3.8 (PVSS), W11.1
VBUS: C5.2, D2.1 (A1), F1.1, J7.A9 (VBUS), J7.B9 (VBUS), W1.1

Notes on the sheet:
1500mA (Common Value)
Current Sensing
Low pass Filter
ESD Protection
Limits inrush current
